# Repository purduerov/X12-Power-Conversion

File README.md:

# Readme for X12-Power-Conversion

Whenever you make a new part, download the datasheet and save it here _**and**_ with the part in the parts library

Always pull other people's changes before beginning to work
`git pull`

Be sure to push your changes after  working on them. Run:
1. `git add .` to add any files in this directory or a subdirectory
or `git add -u` to add any modified files
2. (Optional) `git clean -nX` to see what ignored files can be removed
	`git clean -fX` removes ignored files (Eagle backups)
3. `git commit -m "helpful commit message"` with a description of the work that you did
4. `git push` to push your work to github

Other helpful commands
* `git status` says information about modified and staged files
* `git log` shows the recent commits of the repository
* `git log filename.extension` show the recent commits for just that file
* `git checkout first-couple-letter-of-commit-id` lets you go back to a previous version
* `git checkout master` brings you back to the latest commit
* `git tag` lists the tags
* `git tag -a orderX -m "the version of the board placed for the X'th order"` tag a specific commit
* `git push --tags` needed to push tags to remote
* `git show orderX` show the commit log for the given tag
* `git checkout orderX` go back and interact with the files at the tagged commit

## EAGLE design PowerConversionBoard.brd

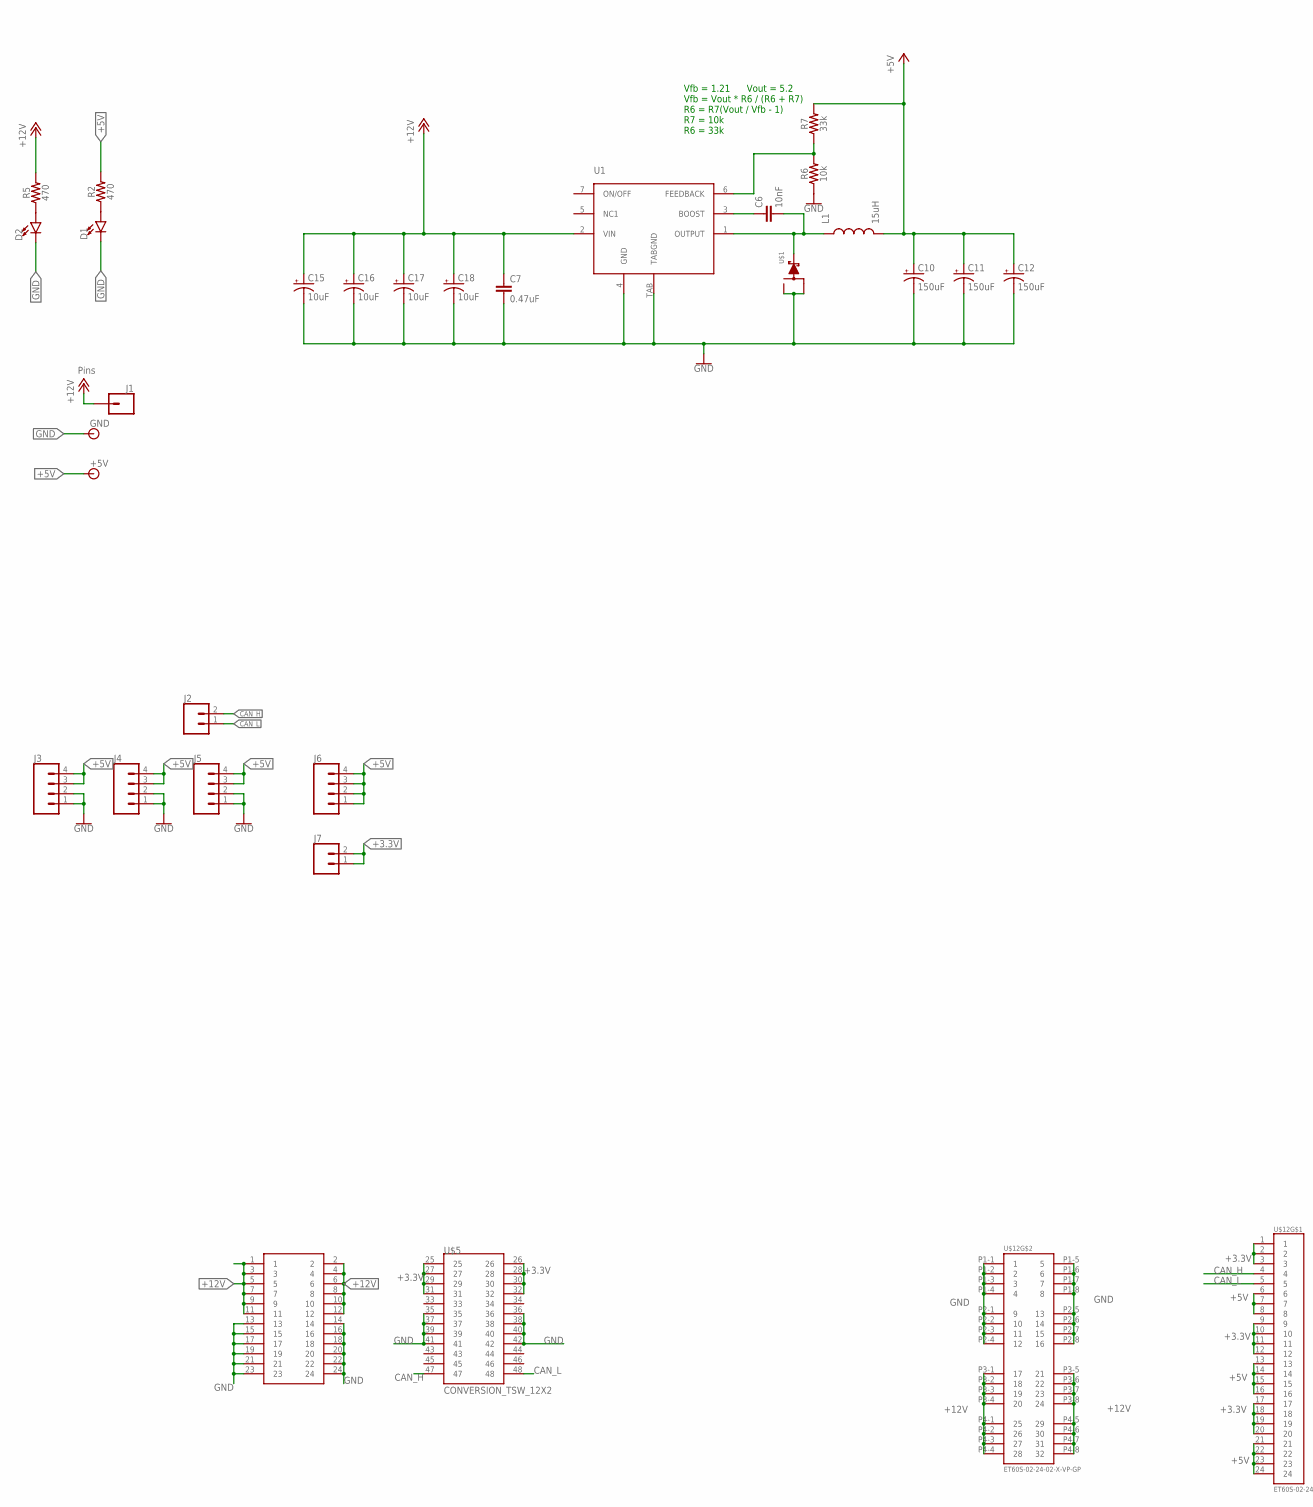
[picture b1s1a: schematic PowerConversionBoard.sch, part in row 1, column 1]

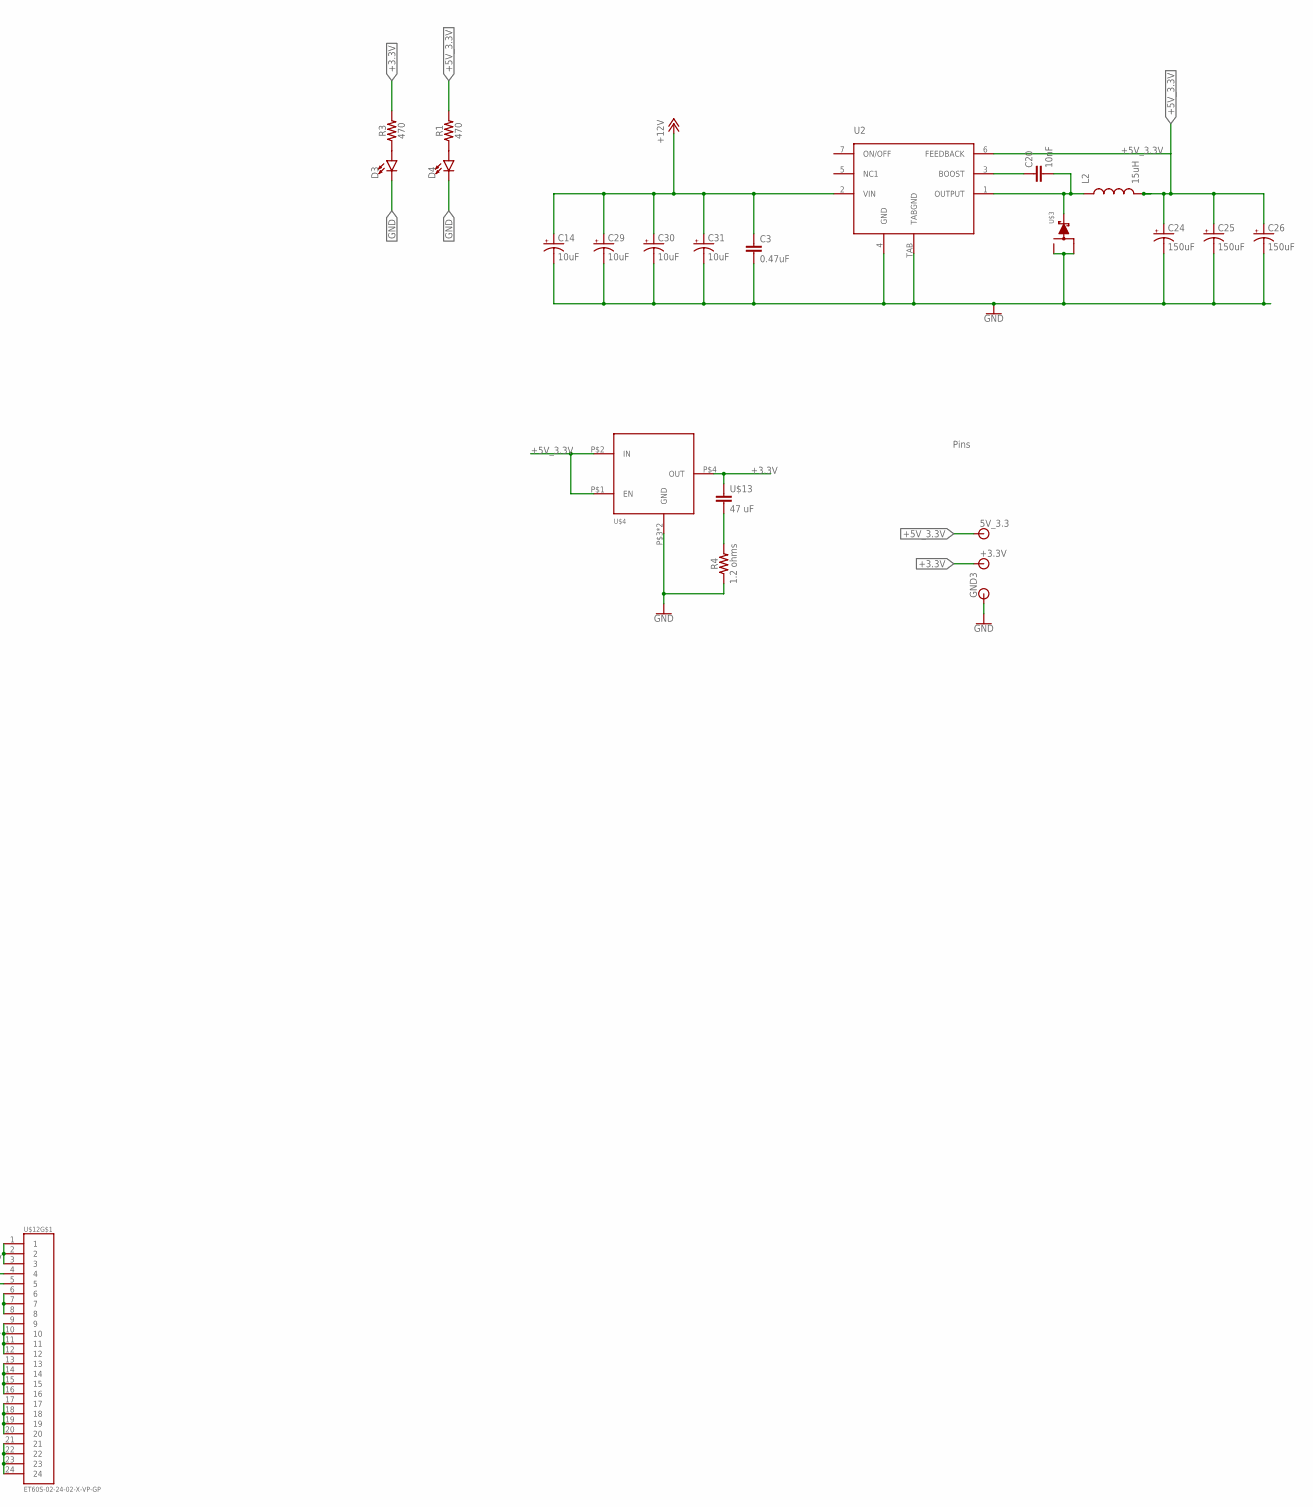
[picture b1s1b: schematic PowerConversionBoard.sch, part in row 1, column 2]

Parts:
5V_3.3: BANANA_CONN
+3.3V, +5V: BANANA_CONN
C3, C7: 0.47uF; C0603
C6, C20: 10nF; 0603
C10, C11, C12, C24, C25, C26: 150uF; CTAN(7.30_4.30MM)
C14, C15, C16, C17, C18, C29, C30, C31: 10uF; CTAN(7.30_4.30MM)
D1, D2, D3, D4: LED0603; LED-0603
GND, GND3: BANANA_CONN
J1: CONN_01; 1X01
J2, J7: CONN_02; 1X02
J3, J4, J5, J6: CONN_04; 1X04
L1, L2: 15uH; HCMA1305
R1, R2, R3, R5: 470; 0603
R4: 1.2 ohms; 0603
R6: 10k; 0603
R7: 33k; 0603
U1, U2: LM2678
U$1, U$3: SWITCHMODE_SCHOTTKY; DPAK-3
U$4: TO-263
U$5: CONVERSION_TSW_12X2
U$12: ET60S-02-24-02-X-VP-GP
U$13: 47 uF; RESC0603_N

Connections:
+3.3V: +3.3V.P$1, J7.1, J7.2, R3.2, U$4.P$4 (OUT), U$5.25, U$5.26, U$5.27, U$5.28, U$5.29, U$5.30, U$5.31, U$5.32, U$12.1, U$12.2, U$12.3, U$12.9, U$12.10, U$12.11, U$12.12, U$12.17, U$12.18, U$12.19, U$12.20, U$13.1
+5V: +5V.P$1, C10.+, C11.+, C12.+, J3.3, J3.4, J4.3, J4.4, J5.3, J5.4, J6.1, J6.2, J6.3, J6.4, L1.2, R2.2, R7.2, U$12.6, U$12.7, U$12.8, U$12.13, U$12.14, U$12.15, U$12.16, U$12.21, U$12.22, U$12.23, U$12.24
+5V_3.3V: 5V_3.3.P$1, C24.+, C25.+, C26.+, L2.2, R1.2, U2.6 (FEEDBACK), U$4.P$1 (EN), U$4.P$2 (IN)
+12V: C3.1, C7.1, C14.+, C15.+, C16.+, C17.+, C18.+, C29.+, C30.+, C31.+, J1.1, R5.2, U1.2 (VIN), U2.2 (VIN), U$5.1, U$5.2, U$5.3, U$5.4, U$5.5, U$5.6, U$5.7, U$5.8, U$5.9, U$5.10, U$5.11, U$5.12, U$12.P3-1 (17), U$12.P3-2 (18), U$12.P3-3 (19), U$12.P3-4 (20), U$12.P3-5 (21), U$12.P3-6 (22), U$12.P3-7 (23), U$12.P3-8 (24), U$12.P4-1 (25), U$12.P4-2 (26), U$12.P4-3 (27), U$12.P4-4 (28), U$12.P4-5 (29), U$12.P4-6 (30), U$12.P4-7 (31), U$12.P4-8 (32)
BST: C6.1, U1.3 (BOOST)
BST_5_3: C20.1, U2.3 (BOOST)
CAN_H: J2.2, U$5.47, U$12.4
CAN_L: J2.1, U$5.48, U$12.5
FB: R6.2, R7.1, U1.6 (FEEDBACK)
GND: C3.2, C7.2, C10.-, C11.-, C12.-, C14.-, C15.-, C16.-, C17.-, C18.-, C24.-, C25.-, C26.-, C29.-, C30.-, C31.-, D1.C, D2.C, D3.C, D4.C, GND.P$1, GND3.P$1, J3.1, J3.2, J4.1, J4.2, J5.1, J5.2, R4.1, R6.1, U1.4 (GND), U1.TAB (TABGND), U2.4 (GND), U2.TAB (TABGND), U$1.P$1, U$1.P$3, U$3.P$1, U$3.P$3, U$4.P$3 (GND), U$4.P$6 (GND), U$5.13, U$5.14, U$5.15, U$5.16, U$5.17, U$5.18, U$5.19, U$5.20, U$5.21, U$5.22, U$5.23, U$5.24, U$5.35, U$5.36, U$5.37, U$5.38, U$5.39, U$5.40, U$5.41, U$5.42, U$12.P1-1 (1), U$12.P1-2 (2), U$12.P1-3 (3), U$12.P1-4 (4), U$12.P1-5 (5), U$12.P1-6 (6), U$12.P1-7 (7), U$12.P1-8 (8), U$12.P2-1 (9), U$12.P2-2 (10), U$12.P2-3 (11), U$12.P2-4 (12), U$12.P2-5 (13), U$12.P2-6 (14), U$12.P2-7 (15), U$12.P2-8 (16)
unnamed: D2.A, R5.1
unnamed: D3.A, R3.1
unnamed: D4.A, R1.1
unnamed: D1.A, R2.1
unnamed: R4.2, U$13.2
SW_5: C6.2, L1.1, U1.1 (OUTPUT), U$1.P$4
SW_5_3: C20.2, L2.1, U2.1 (OUTPUT), U$3.P$4

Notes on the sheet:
Pins
Vfb = 1.21 Vout = 5.2 Vfb = Vout * R6 / (R6 + R7) R6 = R7(Vout / Vfb - 1) R7 = 10k R6 = 33k

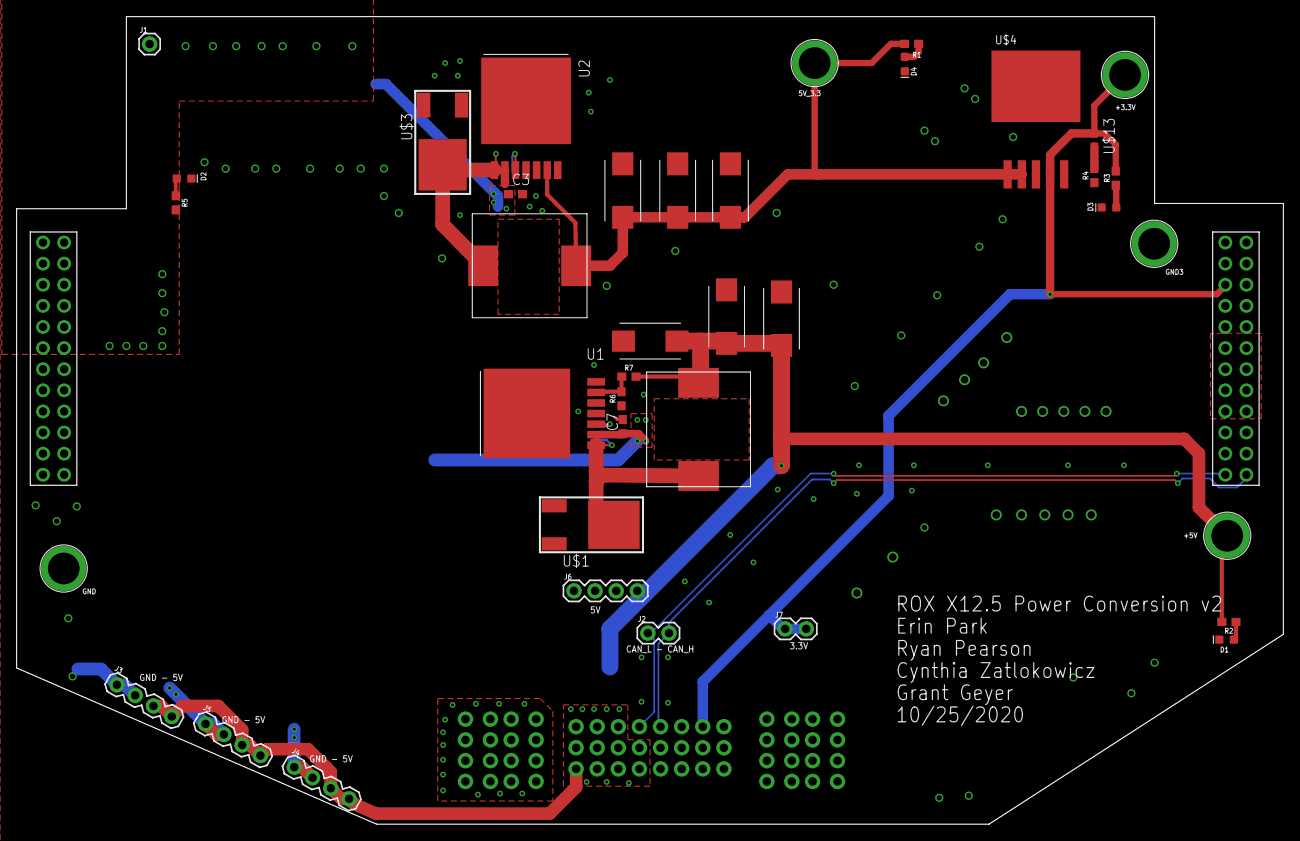
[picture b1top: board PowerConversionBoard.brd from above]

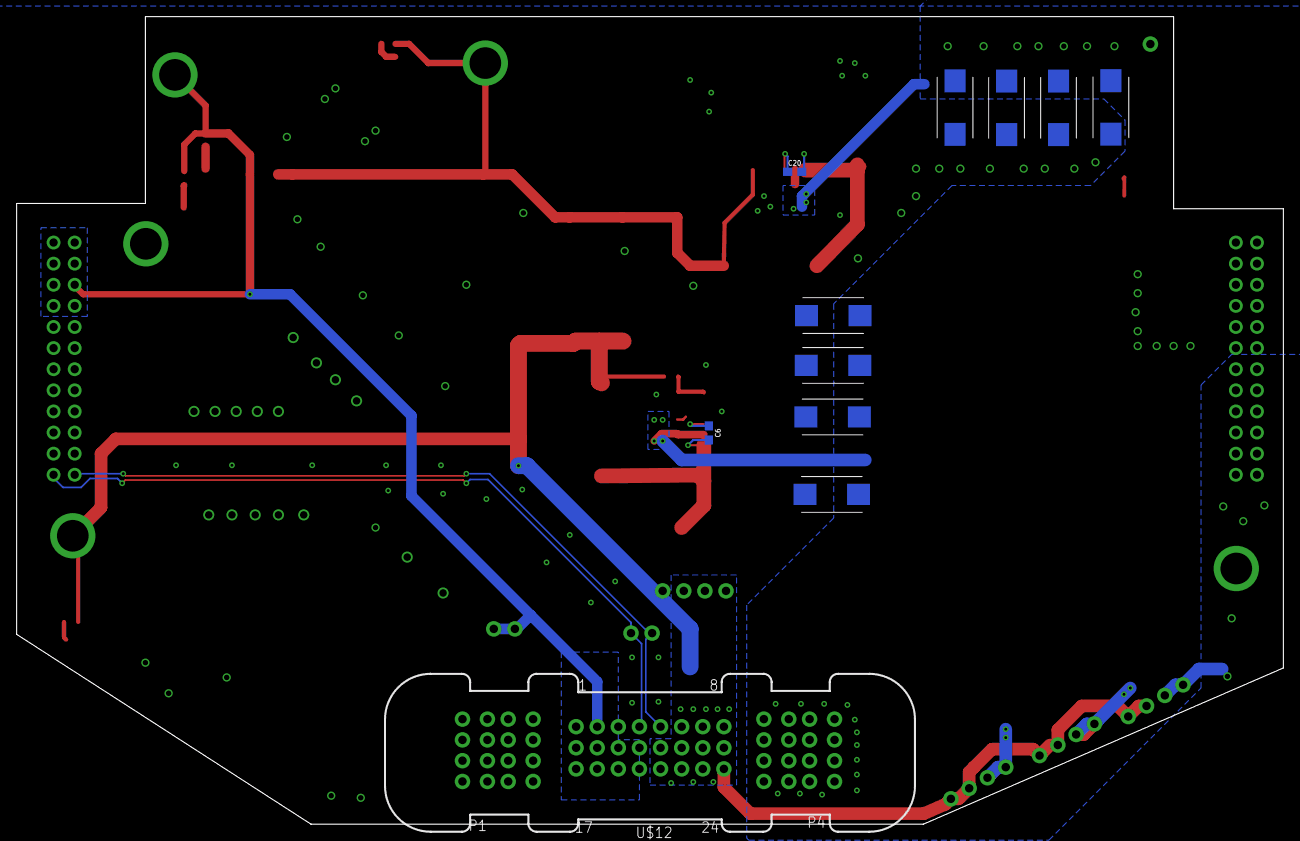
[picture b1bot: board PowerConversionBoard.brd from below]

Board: 2 copper layers, 152.4 x 97.2 mm, 51 parts (11 on the bottom side), 17 nets.

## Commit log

2019-09-25 created schematic
2019-09-25 test
2019-09-28 preliminary crap
2019-09-28 removed library file - need to use x12-parts-library
2019-09-28 fixing local copy
2019-09-28 Grid size changed to 0.01 in - same as last years
2019-09-28 saving changes
2019-10-02 Good Inductor
2019-10-02 note
2019-10-09 Added LEDs to schematic
2019-10-09 Put in good LEDs
2019-10-16 Powerpoint
    test
2019-10-19 Added board, removed powerpoint
2019-10-19 Added LED and test points
2019-10-23 board work
2019-10-26 worked on board
2019-11-02 updated board
2019-11-04 Did some stuff
2019-11-05 done
2019-11-05 added connector for backplane
2019-11-07 power plane
2019-11-07 plane ez
2019-11-07 ez fix
2019-11-08 good progress
2019-11-09 Fixed all errors
2019-11-09 Final touch
2019-11-10 fixed the forward/backward annotation error
2019-11-11 fixed weird
2019-11-13 Board presentation file
2019-11-15 Added ground planes
2019-11-15 adjusted isolate on top plane
2019-11-16 Plane Updates
2019-11-17 bunch of plane things and fixing weird shapes
2019-11-18 plane stuff, 12v op now
2019-11-24 Moved the gnd pin and tp
2019-12-21 Final review session work
    Made 12v bigger
    fixed all remaining drc stubs etc
    some polygon changes
    Remaining work: Make the names for the volt test points bigger
    find a picture to put on there
2020-01-01 added bandana cat
2020-09-09 CAD for connectors
2020-09-12 New stuff to do:
    smaller linear regulator for 3.3v
    make board smaller according to size given later
2020-10-23 chopped off corners
2020-10-26 stupid outline. extra breakouts. tighter layout.
2020-11-04 fix bad merge
2020-11-21 added resistors for adjustable and re aligned schematic

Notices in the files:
parts and their libraries:
SparkFun-Capacitors: Licensing: Creative Commons ShareAlike 4.0 International - https://creativecommons.org/licenses/by-sa/4.0
